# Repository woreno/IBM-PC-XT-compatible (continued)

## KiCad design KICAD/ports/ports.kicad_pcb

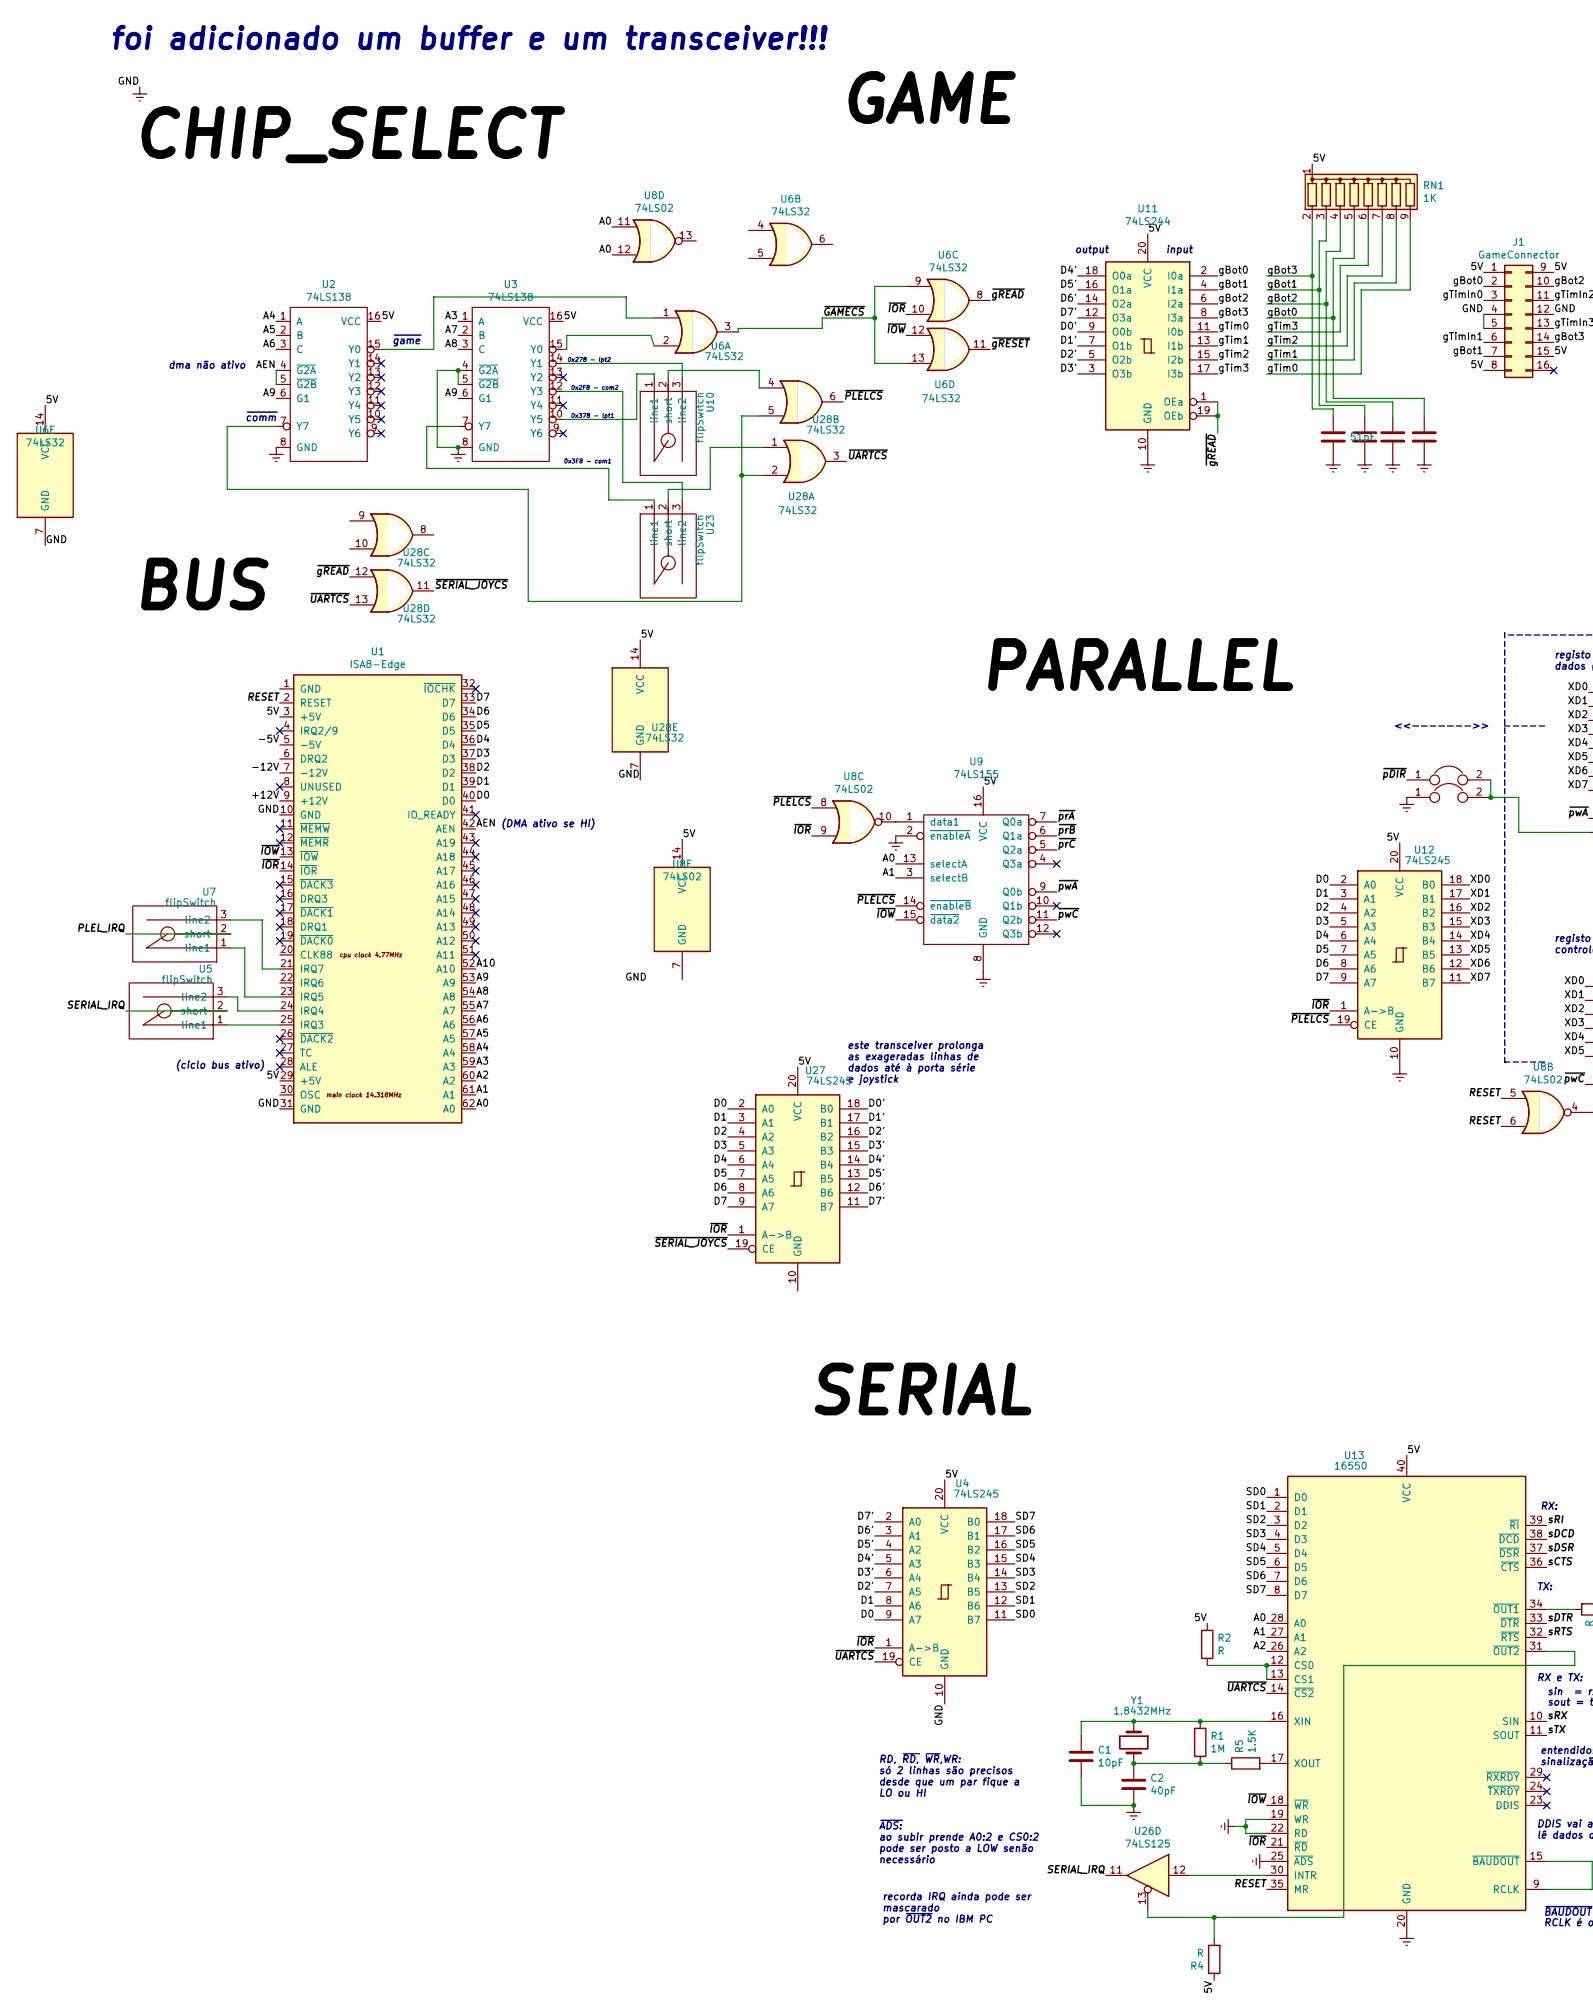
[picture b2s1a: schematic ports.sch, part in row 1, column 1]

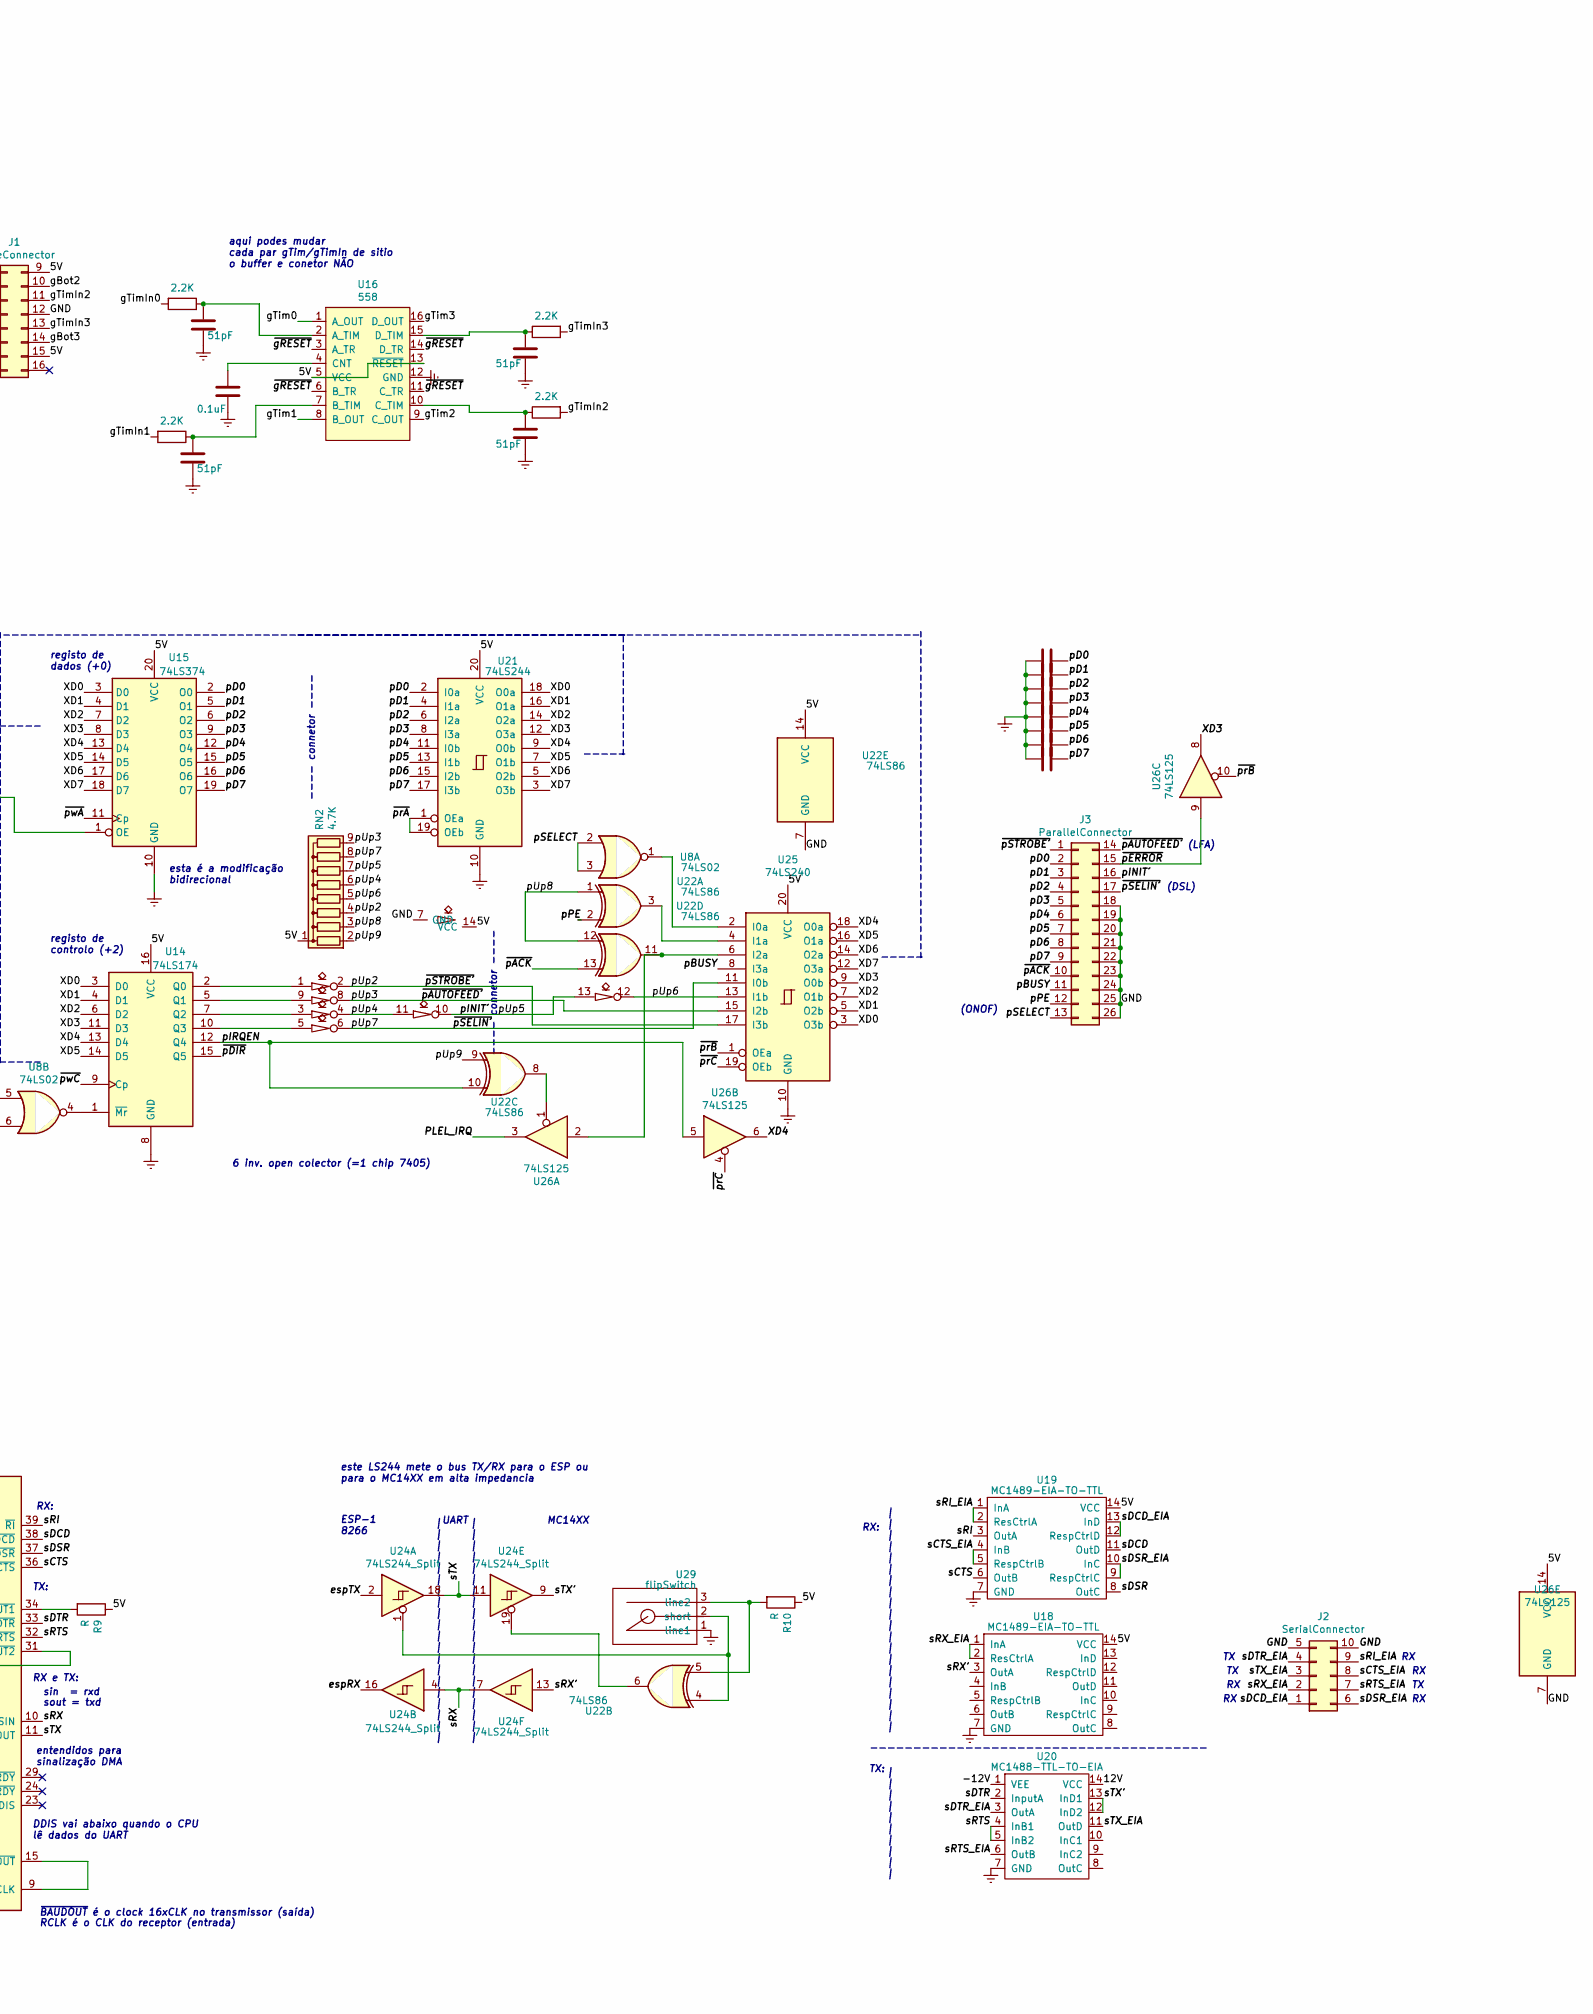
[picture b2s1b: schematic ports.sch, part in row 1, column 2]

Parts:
C1: 10pF; standard_2pins_half
C2: 40pF; standard_2pins
C3, C4, C5, C8, C10, C12, C14, C15: C; standard_2pins
C6: 51pF; standard_2pins
C7: 0.1uF; standard_2pins_half
C9, C11, C13: C; standard_2pins_half
C16, C17, C18, C19: 51pF; standard_2pins_half
J1: GameConnector; Conector2x8_Oval_updown
J2: SerialConnector; Conector2x5_Oval_downup
J3: ParallelConnector; Conector2x13_Oval_updown
JP5, JP6: Jumper; jumper_set_1
R1: 1M; standard_2pins
R2, R4, R9, R10: R; standard_2pins
R3, R6, R7, R8: 2.2K; standard_2pins
R5: 1.5K; standard_2pins
RN1: 1K; R_Array_SIP9
RN2: 4.7K; R_Array_SIP9
U1: ISA8-Edge; ISA_8bit_edge
U2, U3: 74LS138; standard_DIP_16OvalPins
U4, U12, U27: 74LS245; standard_DIP_20pins_thin_body
U5, U7, U10, U23, U29: flipSwitch; mini_flipswitch2.54
U6, U28: 74LS32; standard_DIP_14OvalPins
U8: 74LS02; standard_DIP_14OvalPins
U9: 74LS155; standard_DIP_16OvalPins
U11, U21: 74LS244; standard_DIP_20pins_thin_body
U13: 16550; standard_DIP_40pins_doubleBody_thinpins
U14: 74LS174; standard_DIP_16OvalPins
U15: 74LS374; standard_DIP_20pins_thin_body
U16: 558; standard_DIP_16OvalPins
U17: 7405; standard_DIP_14OvalPins
U18, U19: MC1489-EIA-TO-TTL; standard_DIP_14OvalPins
U20: MC1488-TTL-TO-EIA; standard_DIP_14OvalPins
U22: 74LS86; standard_DIP_14OvalPins
U24: 74LS244_Split; standard_DIP_20pins_thin_body
U25: 74LS240; standard_DIP_20pins_thin_body
U26: 74LS125; standard_DIP_14OvalPins
Y1: 1.8432MHz; standard_2pins

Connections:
/5V: J1.1, J1.8, J1.9, J1.15, R2.1, R4.1, R9.1, R10.1, RN1.1 (common), RN2.1 (common), U1.3 (+5V), U1.29 (+5V), U2.16 (VCC), U3.16 (VCC), U4.20 (VCC), U6.14 (VCC), U8.14 (VCC), U9.16 (VCC), U11.20 (VCC), U12.20 (VCC), U13.40 (VCC), U14.16 (VCC), U15.20 (VCC), U16.5 (VCC), U16.13 (~RESET), U17.14 (VCC), U18.14 (VCC), U19.14 (VCC), U21.20 (VCC), U22.14 (VCC), U25.20 (VCC), U26.14 (VCC), U27.20 (VCC), U28.14 (VCC)
/12V: U20.14 (VCC)
/+12V: U1.9 (+12V)
/-5V: U1.5 (-5V)
/-12V: U1.7 (-12V), U20.1 (VEE)
/A0: U1.62 (A0), U8.11, U8.12, U9.13 (selectA), U13.28 (A0)
/A1: U1.61 (A1), U9.3 (selectB), U13.27 (A1)
/A2: U1.60 (A2), U13.26 (A2)
/A3: U1.59 (A3), U3.1 (A)
/A4: U1.58 (A4), U2.1 (A)
/A5: U1.57 (A5), U2.2 (B)
/A6: U1.56 (A6), U2.3 (C)
/A7: U1.55 (A7), U3.2 (B)
/A8: U1.54 (A8), U3.3 (C)
/A9: U1.53 (A9), U2.6 (G1), U3.6 (G1)
/A10: U1.52 (A10)
/AEN: U1.42 (AEN), U2.4 (~G2A), U2.5 (~G2B)
/D0: U1.40 (D0), U4.9 (A7), U12.2 (A0), U27.2 (A0)
/D0': U11.9 (O0b), U27.18 (B0)
/D1: U1.39 (D1), U4.8 (A6), U12.3 (A1), U27.3 (A1)
/D1': U11.7 (O1b), U27.17 (B1)
/D2: U1.38 (D2), U12.4 (A2), U27.4 (A2)
/D2': U4.7 (A5), U11.5 (O2b), U27.16 (B2)
/D3: U1.37 (D3), U12.5 (A3), U27.5 (A3)
/D3': U4.6 (A4), U11.3 (O3b), U27.15 (B3)
/D4: U1.36 (D4), U12.6 (A4), U27.6 (A4)
/D4': U4.5 (A3), U11.18 (O0a), U27.14 (B4)
/D5: U1.35 (D5), U12.7 (A5), U27.7 (A5)
/D5': U4.4 (A2), U11.16 (O1a), U27.13 (B5)
/D6: U1.34 (D6), U12.8 (A6), U27.8 (A6)
/D6': U4.3 (A1), U11.14 (O2a), U27.12 (B6)
/D7: U1.33 (D7), U12.9 (A7), U27.9 (A7)
/D7': U4.2 (A0), U11.12 (O3a), U27.11 (B7)
/PLEL_IRQ: U7.2 (short), U26.3
/RESET: U1.2 (RESET), U8.5, U8.6, U13.35 (MR)
/SD0: U4.11 (B7), U13.1 (D0)
/SD1: U4.12 (B6), U13.2 (D1)
/SD2: U4.13 (B5), U13.3 (D2)
/SD3: U4.14 (B4), U13.4 (D3)
/SD4: U4.15 (B3), U13.5 (D4)
/SD5: U4.16 (B2), U13.6 (D5)
/SD6: U4.17 (B1), U13.7 (D6)
/SD7: U4.18 (B0), U13.8 (D7)
/SERIAL_IRQ: U5.2 (short), U26.11
/XD0: U12.18 (B0), U14.3 (D0), U15.3 (D0), U21.18 (O0a), U25.3 (O3b)
/XD1: U12.17 (B1), U14.4 (D1), U15.4 (D1), U21.16 (O1a), U25.5 (O2b)
/XD2: U12.16 (B2), U14.6 (D2), U15.7 (D2), U21.14 (O2a), U25.7 (O1b)
/XD3: U12.15 (B3), U14.11 (D3), U15.8 (D3), U21.12 (O3a), U25.9 (O0b), U26.8
/XD4: U12.14 (B4), U14.13 (D4), U15.13 (D4), U21.9 (O0b), U25.18 (O0a), U26.6
/XD5: U12.13 (B5), U14.14 (D5), U15.14 (D5), U21.7 (O1b), U25.16 (O1a)
/XD6: U12.12 (B6), U15.17 (D6), U21.5 (O2b), U25.14 (O2a)
/XD7: U12.11 (B7), U15.18 (D7), U21.3 (O3b), U25.12 (O3a)
/espRX: U24.16
/espTX: U24.2
/gBot0: C3.1, J1.2, RN1.5 (R4), U11.2 (I0a)
/gBot1: C4.1, J1.7, RN1.3 (R2), U11.4 (I1a)
/gBot2: C5.1, J1.10, RN1.4 (R3), U11.6 (I2a)
/gBot3: C6.1, J1.14, RN1.2 (R1), U11.8 (I3a)
/gTim0: RN1.9 (R8), U11.11 (I0b), U16.1 (A_OUT)
/gTim1: RN1.8 (R7), U11.13 (I1b), U16.8 (B_OUT)
/gTim2: RN1.7 (R6), U11.15 (I2b), U16.9 (C_OUT)
/gTim3: RN1.6 (R5), U11.17 (I3b), U16.16 (D_OUT)
/gTimIn0: J1.3, R6.2
/gTimIn1: J1.6, R3.2
/gTimIn2: J1.11, R8.2
/gTimIn3: J1.13, R7.2
/pBUSY: J3.11, U25.8 (I3a)
/pD0: C8.2, J3.2, U15.2 (O0), U21.2 (I0a)
/pD1: C9.2, J3.3, U15.5 (O1), U21.4 (I1a)
/pD2: C10.2, J3.4, U15.6 (O2), U21.6 (I2a)
/pD3: C11.2, J3.5, U15.9 (O3), U21.8 (I3a)
/pD4: C12.2, J3.6, U15.12 (O4), U21.11 (I0b)
/pD5: C13.2, J3.7, U15.15 (O5), U21.13 (I1b)
/pD6: C14.2, J3.8, U15.16 (O6), U21.15 (I2b)
/pD7: C15.2, J3.9, U15.19 (O7), U21.17 (I3b)
/pINIT´: J3.16, RN2.7 (R6), U17.10, U17.13
/pIRQEN: U14.12 (Q4), U22.10, U26.5
/pPE: J3.12, U22.2
/pSELECT: J3.13, U8.2, U8.3
/pUp2: J3.1, RN2.4 (R3), U17.2, U25.17 (I3b)
/pUp3: J3.14, RN2.9 (R8), U17.8, U25.15 (I2b)
/pUp4: RN2.6 (R5), U17.4, U17.11
/pUp6: RN2.5 (R4), U17.12, U25.13 (I1b)
/pUp7: J3.17, RN2.8 (R7), U17.6, U25.11 (I0b)
/pUp8: RN2.3 (R2), U22.1, U22.12
/pUp9: RN2.2 (R1), U22.9
/sCTS: U13.36 (~CTS~), U19.6 (OutB)
/sCTS_EIA: J2.8, U19.4 (InB), U19.5 (RespCtrlB)
/sDCD: U13.38 (~DCD~), U19.11 (OutD)
/sDCD_EIA: J2.1, U19.12 (RespCtrlD), U19.13 (InD)
/sDSR: U13.37 (~DSR~), U19.8 (OutC)
/sDSR_EIA: J2.6, U19.9 (RespCtrlC), U19.10 (InC)
/sDTR: U13.33 (~DTR~), U20.2 (InputA)
/sDTR_EIA: J2.4, U20.3 (OutA)
/sRI: U13.39 (~RI~), U19.3 (OutA)
/sRI_EIA: J2.9, U19.1 (InA), U19.2 (ResCtrlA)
/sRTS: U13.32 (~RTS~), U20.4 (InB1), U20.5 (InB2)
/sRTS_EIA: J2.7, U20.6 (OutB)
/sRX: U13.10 (SIN), U24.4, U24.7
/sRX': U18.3 (OutA), U24.13
/sRX_EIA: J2.2, U18.1 (InA), U18.2 (ResCtrlA)
/sTX: U13.11 (SOUT), U24.11, U24.18
/sTX': U20.12 (InD2), U20.13 (InD1), U24.9
/sTX_EIA: J2.3, U20.11 (OutD)
/~GAMECS: U6.3, U6.9, U6.13
/~IOR: U1.14 (~IOR), U4.1 (A->B), U6.10, U8.9, U12.1 (A->B), U13.21 (~RD~), U27.1 (A->B)
/~IOW: U1.13 (~IOW), U6.12, U9.15 (~data2), U13.18 (~WR~)
/~PLELCS: U8.8, U9.14 (~enableB), U12.19 (CE), U28.6
/~SERIAL_JOYCS: U27.19 (CE), U28.11
/~UARTCS: U4.19 (CE), U13.14 (~CS2~), U28.3, U28.13
/~gREAD: U6.8, U11.1 (OEa), U11.19 (OEb), U28.12
/~gRESET: U6.11, U16.3 (A_TR), U16.6 (B_TR), U16.11 (C_TR), U16.14 (D_TR)
/~pACK: J3.10, U22.13
/~pDIR: JP5.1, U14.15 (Q5)
/~pERROR: J3.15, U26.9
/~prA: U9.7 (Q0a), U21.1 (OEa), U21.19 (OEb)
/~prB: U9.6 (Q1a), U25.1 (OEa), U26.10
/~prC: U9.5 (Q2a), U25.19 (OEb), U26.4
/~pwA: U9.9 (Q0b), U15.11 (Cp)
/~pwC: U9.11 (Q2b), U14.9 (Cp)
Earth: C1.2, C2.2, C3.2, C4.2, C5.2, C6.2, C7.2, C8.1, C9.1, C10.1, C11.1, C12.1, C13.1, C14.1, C15.1, C16.2, C17.2, C18.2, C19.2, J1.4, J1.5, J1.12, J2.5, J2.10, J3.18, J3.19, J3.20, J3.21, J3.22, J3.23, J3.24, J3.25, J3.26, JP6.1, U1.10 (GND), U1.31 (GND), U2.8 (GND), U3.4 (~G2A), U3.5 (~G2B), U3.8 (GND), U4.10 (GND), U6.7 (GND), U9.2 (~enableA), U9.8 (GND), U11.10 (GND), U12.10 (GND), U13.19 (WR), U13.20 (GND), U13.22 (RD), U13.25 (~ADS~), U14.8 (GND), U15.10 (GND), U16.12 (GND), U17.7 (GND), U18.7 (GND), U19.7 (GND), U20.7 (GND), U21.10 (GND), U22.7 (GND), U25.10 (GND), U26.7 (GND), U28.7 (GND), U29.1 (line1)
unnamed: C1.1, R1.1, U13.16 (XIN), Y1.1
unnamed: C2.1, R1.2, R5.1, Y1.2
unnamed: C7.1, U16.4 (CNT)
unnamed: C16.1, R3.1, U16.7 (B_TIM)
unnamed: C17.1, R6.1, U16.2 (A_TIM)
unnamed: C18.1, R7.1, U16.15 (D_TIM)
unnamed: C19.1, R8.1, U16.10 (C_TIM)
unnamed: JP5.2, JP6.2, U15.1 (OE)
unnamed: R2.2, U13.12 (CS0), U13.13 (CS1)
unnamed: R4.2, U13.31 (~OUT2~), U26.13
unnamed: R5.2, U13.17 (XOUT)
unnamed: R9.2, U13.34 (~OUT1~)
unnamed: R10.2, U22.5, U29.3 (line2)
unnamed: U1.21 (IRQ7), U7.3 (line2)
unnamed: U1.23 (IRQ5), U7.1 (line1)
unnamed: U1.24 (IRQ4), U5.3 (line2)
unnamed: U1.25 (IRQ3), U5.1 (line1)
unnamed: U2.7 (Y7), U28.2, U28.5
unnamed: U2.15 (Y0), U6.1
unnamed: U3.15 (Y0), U6.2
unnamed: U8.10, U9.1 (data1)
unnamed: U3.10 (Y5), U10.1 (line1)
unnamed: U10.2 (short), U28.4
unnamed: U3.14 (Y1), U10.3 (line2)
unnamed: U13.9 (RCLK), U13.15 (~BAUDOUT~)
unnamed: U13.30 (INTR), U26.12
unnamed: U8.4, U14.1 (~Mr)
unnamed: U14.2 (Q0), U17.1
unnamed: U14.5 (Q1), U17.9
unnamed: U14.7 (Q2), U17.3
unnamed: U14.10 (Q3), U17.5
unnamed: U22.3, U25.4 (I1a)
unnamed: U22.4, U24.1, U29.2 (short)
unnamed: U22.6, U24.19
unnamed: U22.8, U26.1
unnamed: U22.11, U25.6 (I2a), U26.2
unnamed: U3.7 (Y7), U23.1 (line1)
unnamed: U23.2 (short), U28.1
unnamed: U3.12 (Y3), U23.3 (line2)
unnamed: U8.1, U25.2 (I0a)

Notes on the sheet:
RX:
TX:
sout = txd
sin = rxd
~BAUDOUT~ é o clock 16xCLK no transmissor (saída)
RCLK é o CLK do receptor (entrada)
DDIS vai abaixo quando o CPU lê dados do UART
RD, ~RD, ~WR~,WR: só 2 linhas são precisos desde que um par fique a LO ou HI
~ADS:~ ao subir prende A0:2 e CS0:2 pode ser posto a LOW senão necessário
entendidos para sinalização DMA
RX e TX:
| | | | | | | | | | | | | | | | | | | |
| | | | | | | | | |
---------------------------------------
recorda IRQ ainda pode ser mascarado por ~OUT2~ no IBM PC
(DMA ativo se HI)
(ciclo bus ativo)
dma não ativo
~game
~comm
esta é a modificação bidirecional
<<------->>
--------------------------------------------------
-----
---- connetor ----
------------------------------------------------------------------------
--------------
--------------------------------------
(ONOF)
(DSL)
(LFA)
0x3F8 - com1
0x378 - lpt1
0x2F8 - com2
0x278 - lpt2
output
input
aqui podes mudar cada par gTim/gTimIn de sitio o buffer e conetor NÃO
6 inv. open colector (=1 chip 7405)
registo de dados (+0)

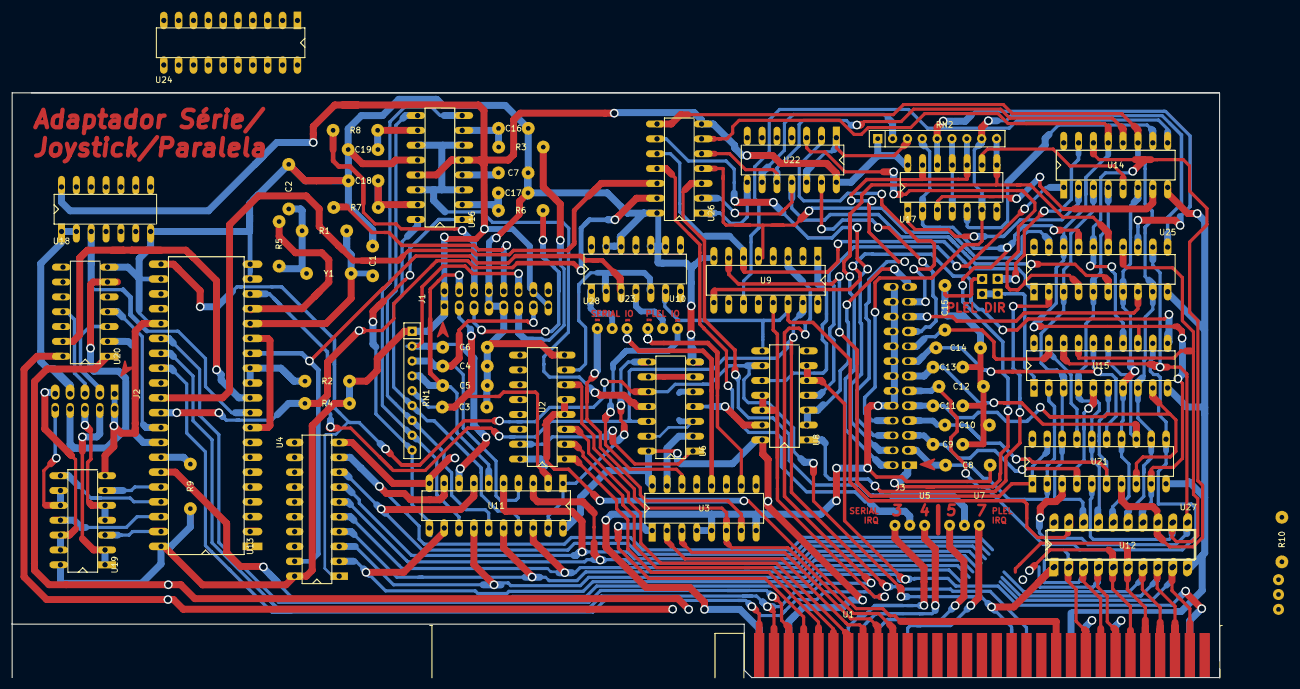
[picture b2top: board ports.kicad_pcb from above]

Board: 2 copper layers, 206.5 x 100.0 mm, 66 parts (0 on the bottom side), 155 nets.
